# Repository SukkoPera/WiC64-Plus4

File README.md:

# WiC+4
WiC+4 is a wireless interface based on the ESP32 chip for the Commodore +4.

## Summary
This is just a customization of [the original WiC64 project](https://github.com/WiC64-Team/wic64-hardware) in order to make it work on the Commodore +4. In fact, while this computer features a User Port that looks very similar to the one you can find on the C64, the electrical connections are different and thus some modifications are required.

The board should also be usable on a C16 or C116 through [a User Port card](https://github.com/SukkoPera/16up).

Apart from the functional changes:
* I have added a jumper that selects whether the ESP should be powered by the rectified +9VAC or by the 5V rail.
* Consequently, I have added a ferrite on the 5V rail. An axial inductor should also fit, some experimentation will show what is better.
* I have switched the resistor footprints to 0805 for easier hand solderability.

The board keeps exactly the same size and major component layout, so all enclosures should still be usable.

## Usage
One of my goals was to make the modifications in a way such that **no changes would be required on the firmware side**.

Nevertheless, **this thing is completely unusable at the moment**, since no computer-side software exists.

What needs to be done is to take [this library](https://github.com/WiC64-Team/wic64-library) and adapt it so that:

* Data I/O takes place through the User Port
* The PC2 signal (ack/strobe: byte read from/written to port, rising edge) is controlled through /DTR
* The PA2 signal (Direction: HIGH = C64/+4 => ESP, LOW = ESP => C64/+4) is controlled through /RTS
* The FLAG2 signal (ack/strobe: byte read from/written to port, falling edge) can be read through /DCD.

/DTR and /RTS can be controlled through bits 0 and 3 (respectively) of $FD02 (Note that there is an inverter gate inbetween, so they are not really active-low).

/DCD can be read through bit 4 of $FD01 (again, mind the inverter gate). An interrupt can also be set up to track its changes if required.

I recommend taking a quick look at the 6551 ACIA datasheet in order to understand how to treat the other bits properly.

Another recommendation would be to make the User Port/ACIA base addresses configurable, for those who might want to use the 16UP board in External mode.

I had actually done part of the above work, only to find out that **I would then need a "launcher" program that is not open source, so I decided to stop all development**.

Please refer to [the original project](https://github.com/WiC64-Team/wic64-hardware) for all documentation, firmware, drivers, etc.

## Assembly
If you decide to use power from the 5V rail, the diode bridge and 220uF cap can be skipped.

The ESP-01 board in the top right corner is only required for debugging.

## Releases
If you want to get this board produced, you are recommended to get [the latest release](https://github.com/SukkoPera/WiC64-Plus4/releases) rather than the current git version, as the latter might be under development and is not guaranteed to be working.

Every release is accompanied by its Bill Of Materials (BOM) file and any relevant notes about it, which you are recommended to read carefully.

## License
WiC+4 is distributed under the [CC-BY 4.0 license](https://creativecommons.org/licenses/by/4.0/).

WiC+4 is provided to you ‘as is’ and without any express or implied warranties whatsoever with respect to its functionality, operability or use, including, without limitation, any implied warranties of merchantability, fitness for a particular purpose or infringement. We expressly disclaim any liability whatsoever for any direct, indirect, consequential, incidental or special damages, including, without limitation, lost revenues, lost profits, losses resulting from business interruption or loss of data, regardless of the form of action or legal theory under which the liability may be asserted, even if advised of the possibility or likelihood of such damages.

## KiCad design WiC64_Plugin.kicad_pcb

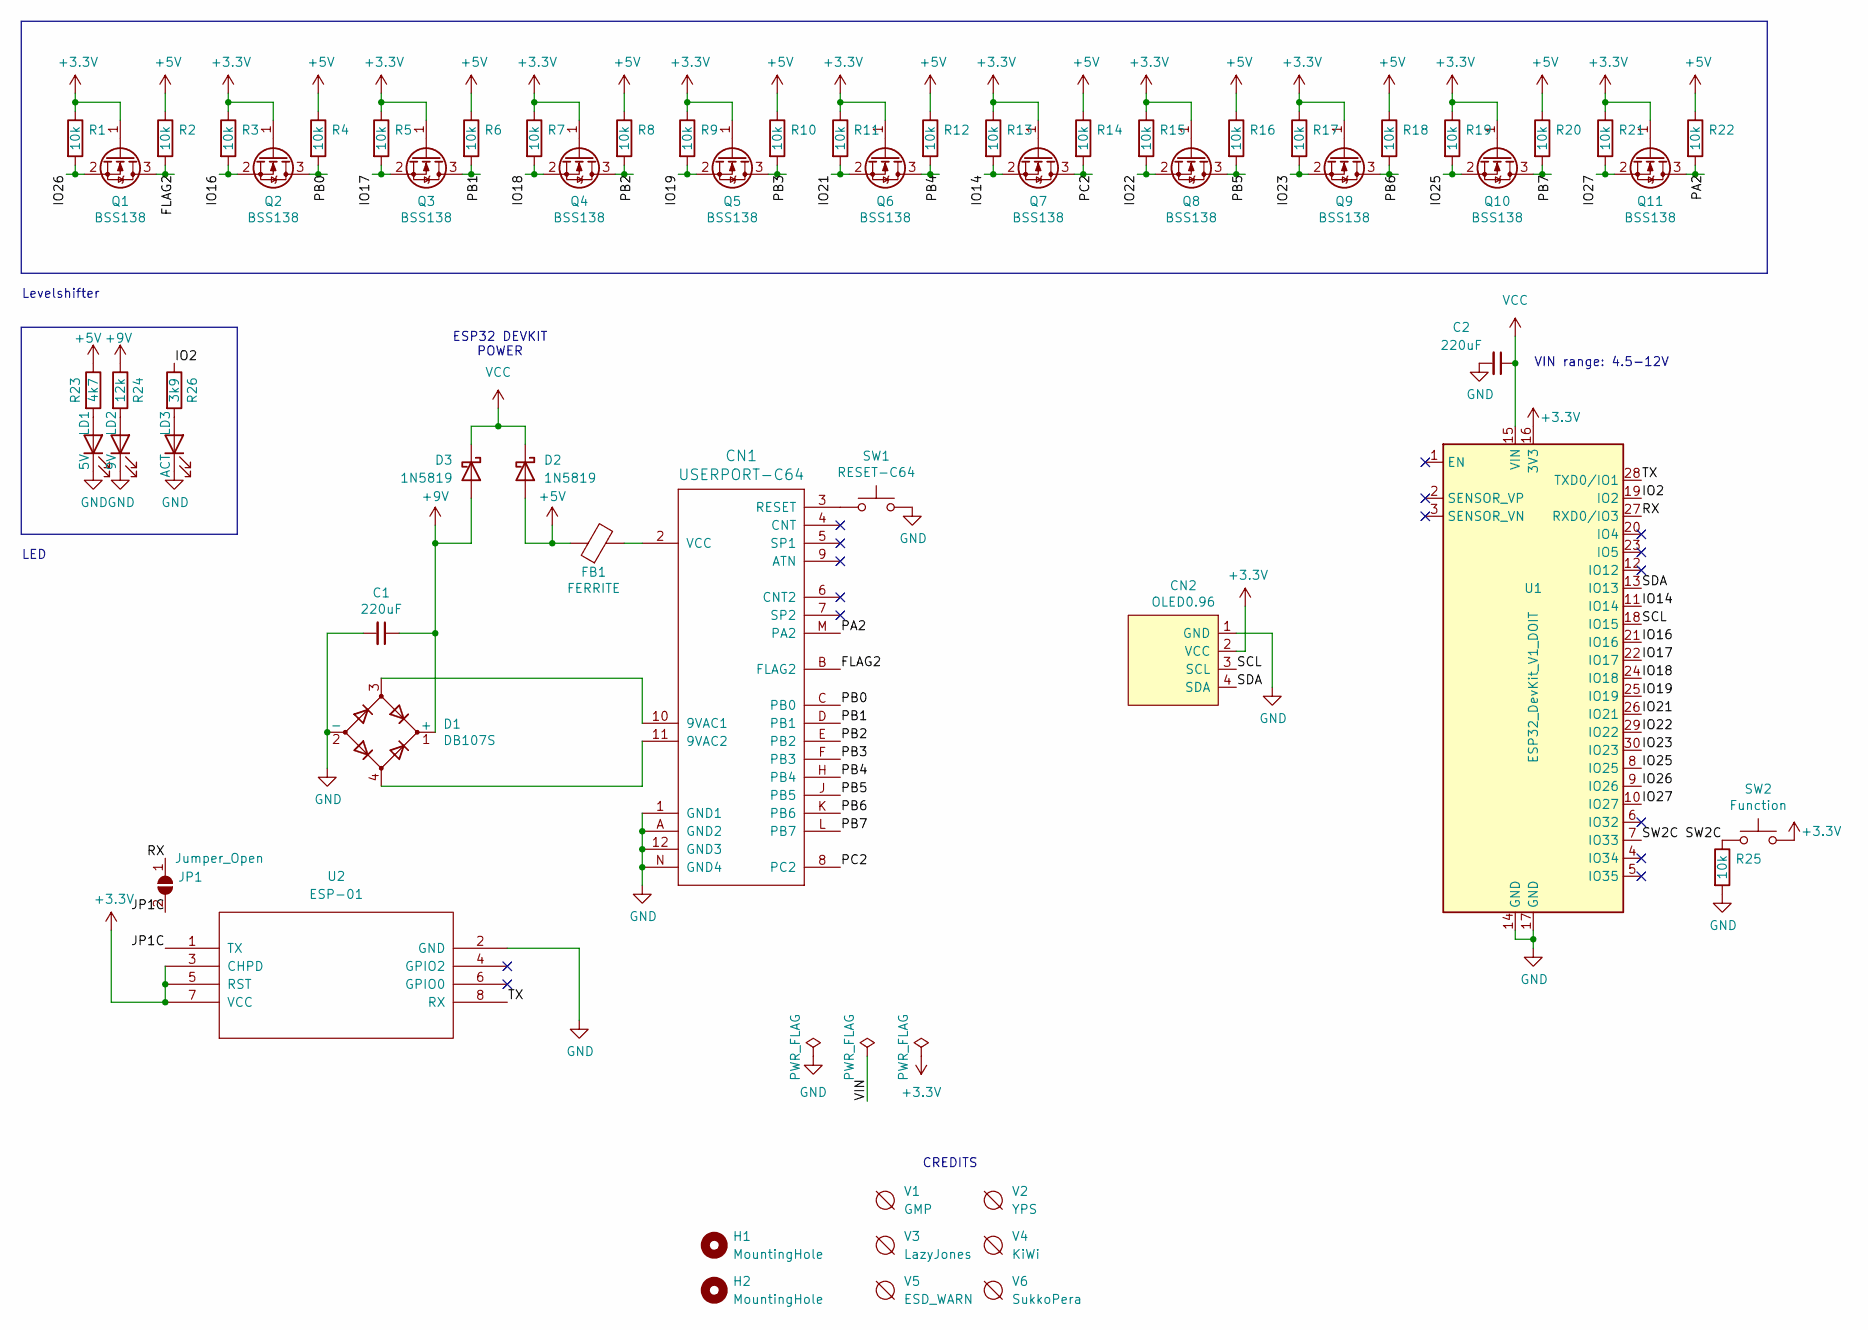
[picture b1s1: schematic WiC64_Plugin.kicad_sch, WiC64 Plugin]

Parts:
C1: 220uF; CP_6.3x11mm_horiz-R; LCSC C269997
C2: 220uF; CP_6.3x11mm_horiz-R; LCSC C106598
CN1: USERPORT-C64; UPS24CONN
CN2: OLED0.96; PinSocket_1x04_P2.54mm_Vertical
D1: DB107S; Diode_Bridge_Diotec_SO-DIL-Slim; LCSC C190797
D2, D3: 1N5819; D_SMA; LCSC C402219
FB1: FERRITE; Ferrite_D6.0mm_L10.00mm_Horizontal
H1, H2: MountingHole; MountingHole_3.2mm_M3_ISO7380
JP1: Jumper_Open; SolderJumper-2_P1.3mm_Open_RoundedPad1.0x1.5mm
LD1: 5V; LED_D3.0mm; LCSC C568936
LD2: 9V; LED_D3.0mm; LCSC C568937
LD3: ACT; LED_D3.0mm; LCSC C331056
Q1, Q2, Q3, Q4, Q5, Q6, Q7, Q8, Q9, Q10, Q11: BSS138; SOT-23; LCSC C112239
R1, R2, R3, R4, R5, R6, R7, R8, R9, R10, R11, R12, R13, R14, R15, R16, R17, R18, R19, R20, R21, R22, R25: 10k; R_0805_2012Metric_Pad1.20x1.40mm_HandSolder; LCSC C25804
R23: 4k7; R_0805_2012Metric_Pad1.20x1.40mm_HandSolder; LCSC C23162
R24: 12k; R_0805_2012Metric_Pad1.20x1.40mm_HandSolder; LCSC C22790
R26: 3k9; R_0805_2012Metric_Pad1.20x1.40mm_HandSolder; LCSC C23018
SW1: RESET-C64; SW_Tactile_SPST_Angled_PTS645Vx58-2LFS; LCSC C406160
SW2: Function; SW_Tactile_SPST_Angled_PTS645Vx58-2LFS; LCSC C406160
U1: ESP32_DevKit_V1_DOIT; esp32_devkit_v1_doit
U2: ESP-01
V1: GMP
V2: YPS; YPS2
V3: LazyJones; LazyJones2
V4: KiWi
V5: ESD_WARN; ESD-Logo_6.6x6mm_SilkScreen
V6: SukkoPera; PearLogo

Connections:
+3.3V: CN2.2 (VCC), Q1.1 (G), Q2.1 (G), Q3.1 (G), Q4.1 (G), Q5.1 (G), Q6.1 (G), Q7.1 (G), Q8.1 (G), Q9.1 (G), Q10.1 (G), Q11.1 (G), R1.1, R3.1, R5.1, R7.1, R9.1, R11.1, R13.1, R15.1, R17.1, R19.1, R21.1, SW2.2, U1.16 (3V3), U2.3 (CHPD), U2.5 (RST), U2.7 (VCC)
+5V: D2.2 (A), FB1.1, R2.1, R4.1, R6.1, R8.1, R10.1, R12.1, R14.1, R16.1, R18.1, R20.1, R22.1, R23.1
+9V: C1.1, D1.1 (+), D3.2 (A), R24.1
/FLAG2: CN1.B (FLAG2), Q1.3 (D), R2.2
/IO2: R26.1, U1.19 (IO2)
/IO14: Q7.2 (S), R13.2, U1.11 (IO14)
/IO16: Q2.2 (S), R3.2, U1.21 (IO16)
/IO17: Q3.2 (S), R5.2, U1.22 (IO17)
/IO18: Q4.2 (S), R7.2, U1.24 (IO18)
/IO19: Q5.2 (S), R9.2, U1.25 (IO19)
/IO21: Q6.2 (S), R11.2, U1.26 (IO21)
/IO22: Q8.2 (S), R15.2, U1.29 (IO22)
/IO23: Q9.2 (S), R17.2, U1.30 (IO23)
/IO25: Q10.2 (S), R19.2, U1.8 (IO25)
/IO26: Q1.2 (S), R1.2, U1.9 (IO26)
/IO27: Q11.2 (S), R21.2, U1.10 (IO27)
/JP1C: JP1.2 (B), U2.1 (TX)
/PA2: CN1.M (PA2), Q11.3 (D), R22.2
/PB0: CN1.C (PB0), Q2.3 (D), R4.2
/PB1: CN1.D (PB1), Q3.3 (D), R6.2
/PB2: CN1.E (PB2), Q4.3 (D), R8.2
/PB3: CN1.F (PB3), Q5.3 (D), R10.2
/PB4: CN1.H (PB4), Q6.3 (D), R12.2
/PB5: CN1.J (PB5), Q8.3 (D), R16.2
/PB6: CN1.K (PB6), Q9.3 (D), R18.2
/PB7: CN1.L (PB7), Q10.3 (D), R20.2
/PC2: CN1.8 (PC2), Q7.3 (D), R14.2
/RX: JP1.1 (A), U1.27 (RXD0/IO3)
/SCL: CN2.3 (SCL), U1.18 (IO15)
/SDA: CN2.4 (SDA), U1.13 (IO13)
/SW2C: R25.1, SW2.1, U1.7 (IO33)
/TX: U1.28 (TXD0/IO1), U2.8 (RX)
GND: C1.2, C2.2, CN1.1 (GND1), CN1.12 (GND3), CN1.A (GND2), CN1.N (GND4), CN2.1 (GND), D1.2 (-), LD1.1 (K), LD2.1 (K), LD3.1 (K), R25.2, SW1.2, U1.14 (GND), U1.17 (GND), U2.2 (GND)
unnamed: CN1.10 (9VAC1), D1.3
unnamed: CN1.11 (9VAC2), D1.4
unnamed: CN1.3 (RESET), SW1.1
unnamed: CN1.2 (VCC), FB1.2
unnamed: LD1.2 (A), R23.2
unnamed: LD2.2 (A), R24.2
unnamed: LD3.2 (A), R26.2
VCC: C2.1, D2.1 (K), D3.1 (K), U1.15 (VIN)

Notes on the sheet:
VIN range: 4.5-12V
CREDITS
Levelshifter
LED
ESP32 DEVKIT POWER

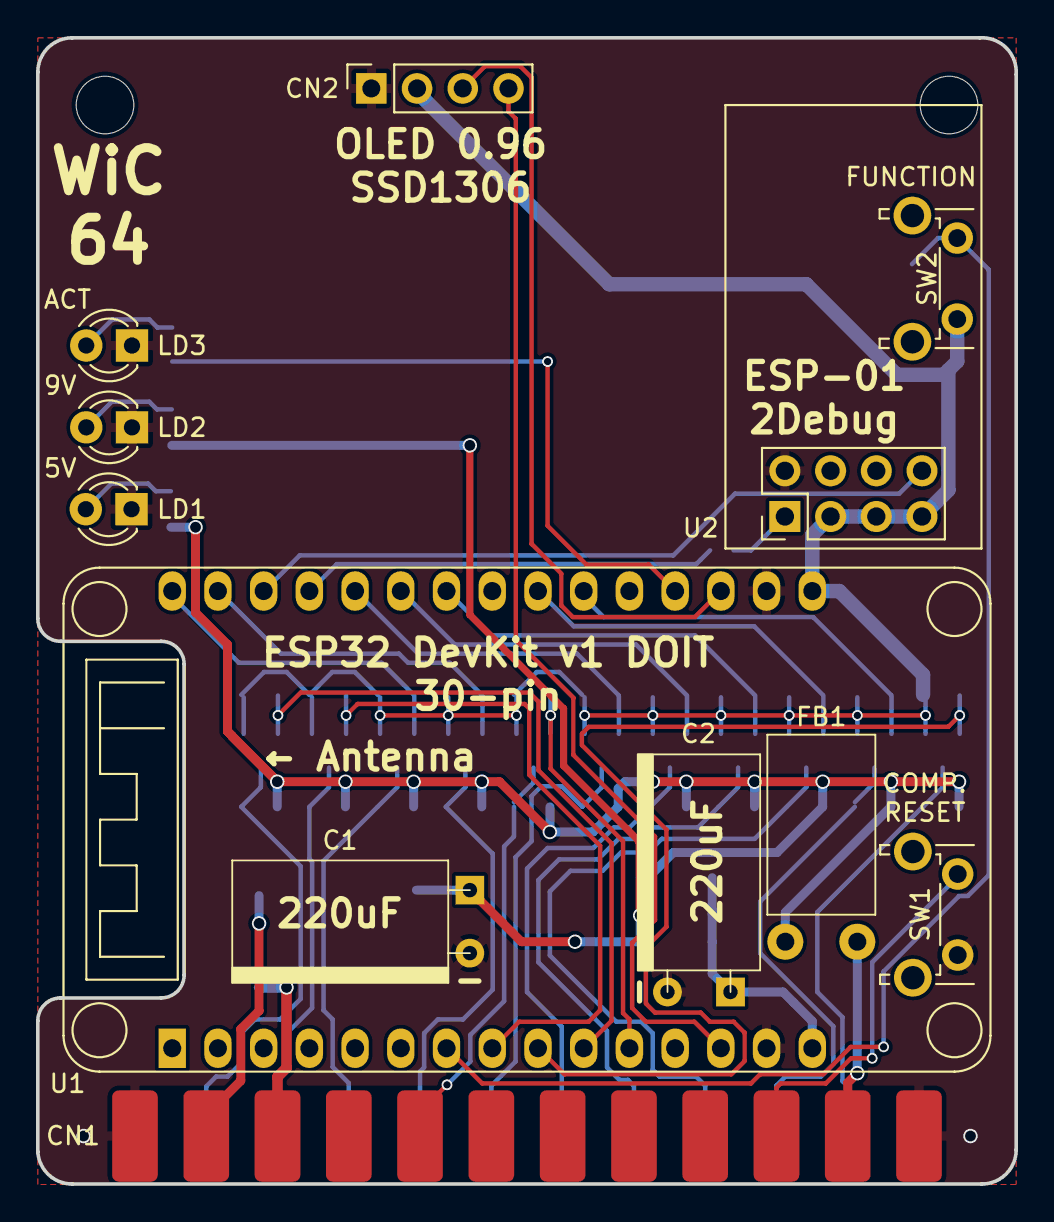
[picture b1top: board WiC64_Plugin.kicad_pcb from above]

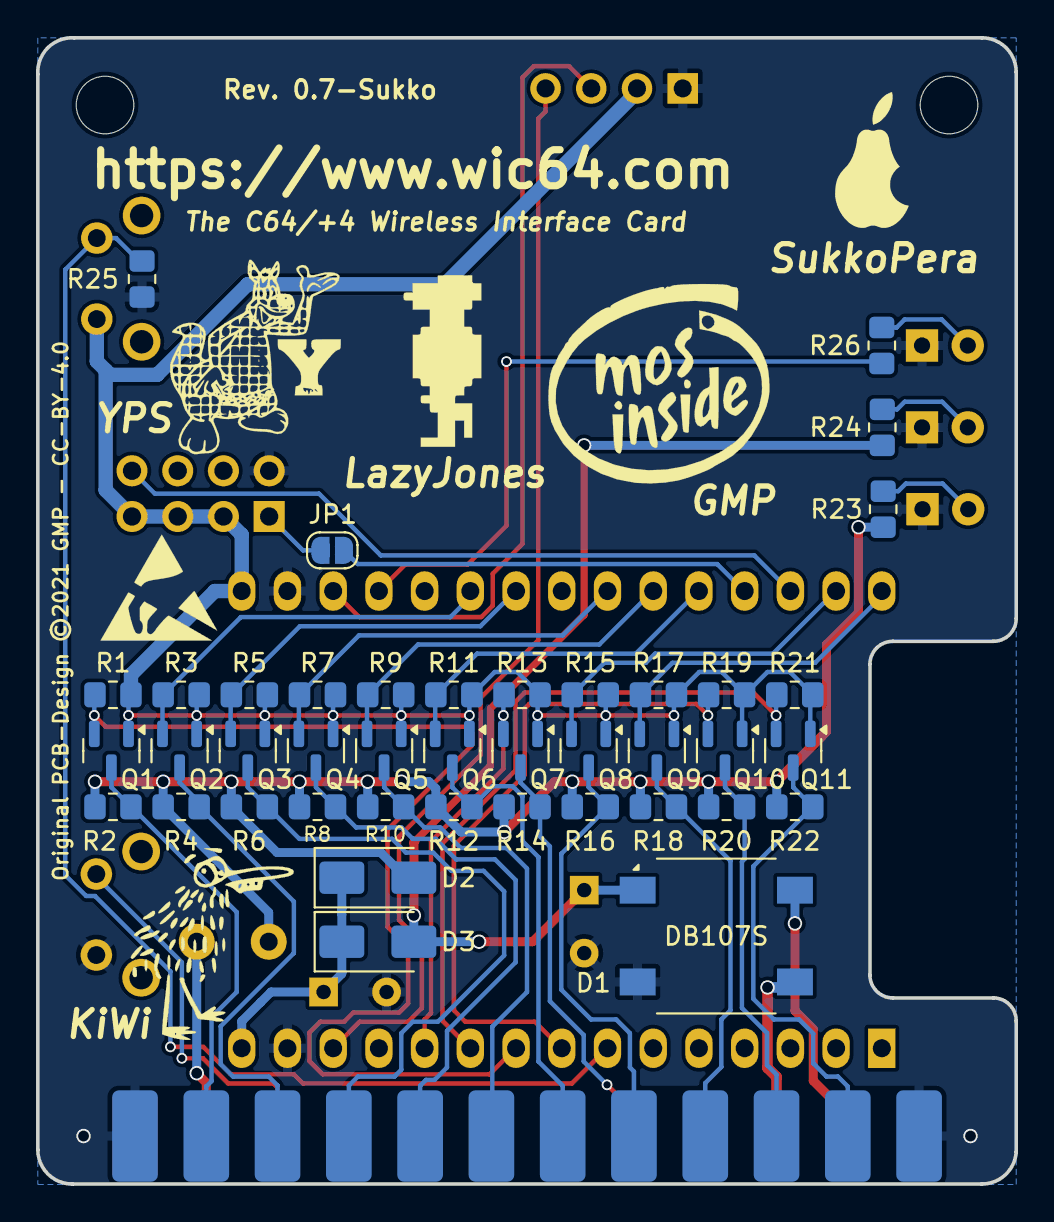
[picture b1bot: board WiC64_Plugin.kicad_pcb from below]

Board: 2 copper layers, 54.4 x 63.7 mm, 61 parts (47 on the bottom side), 41 nets.

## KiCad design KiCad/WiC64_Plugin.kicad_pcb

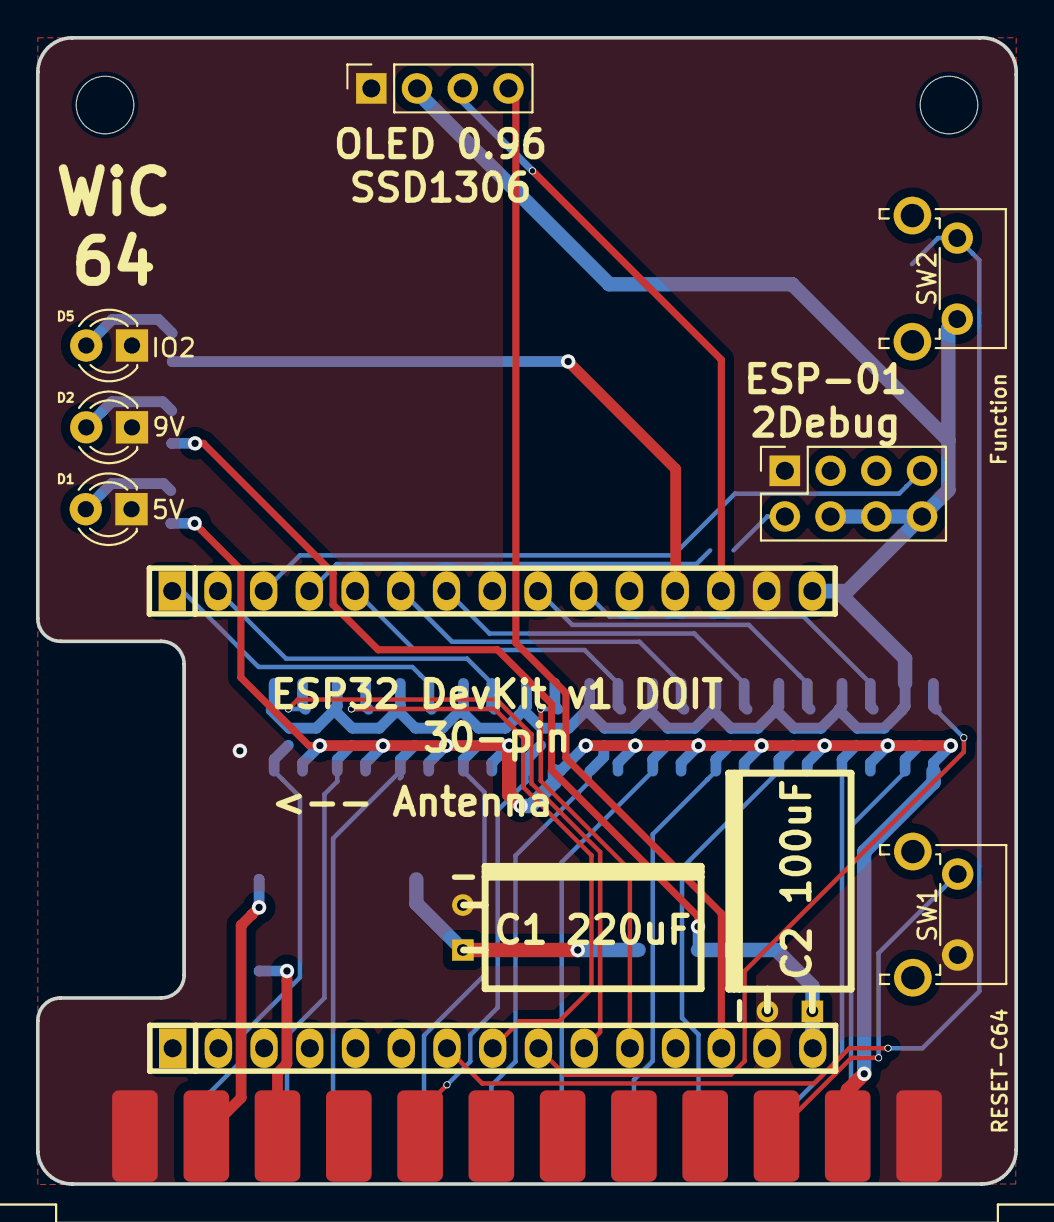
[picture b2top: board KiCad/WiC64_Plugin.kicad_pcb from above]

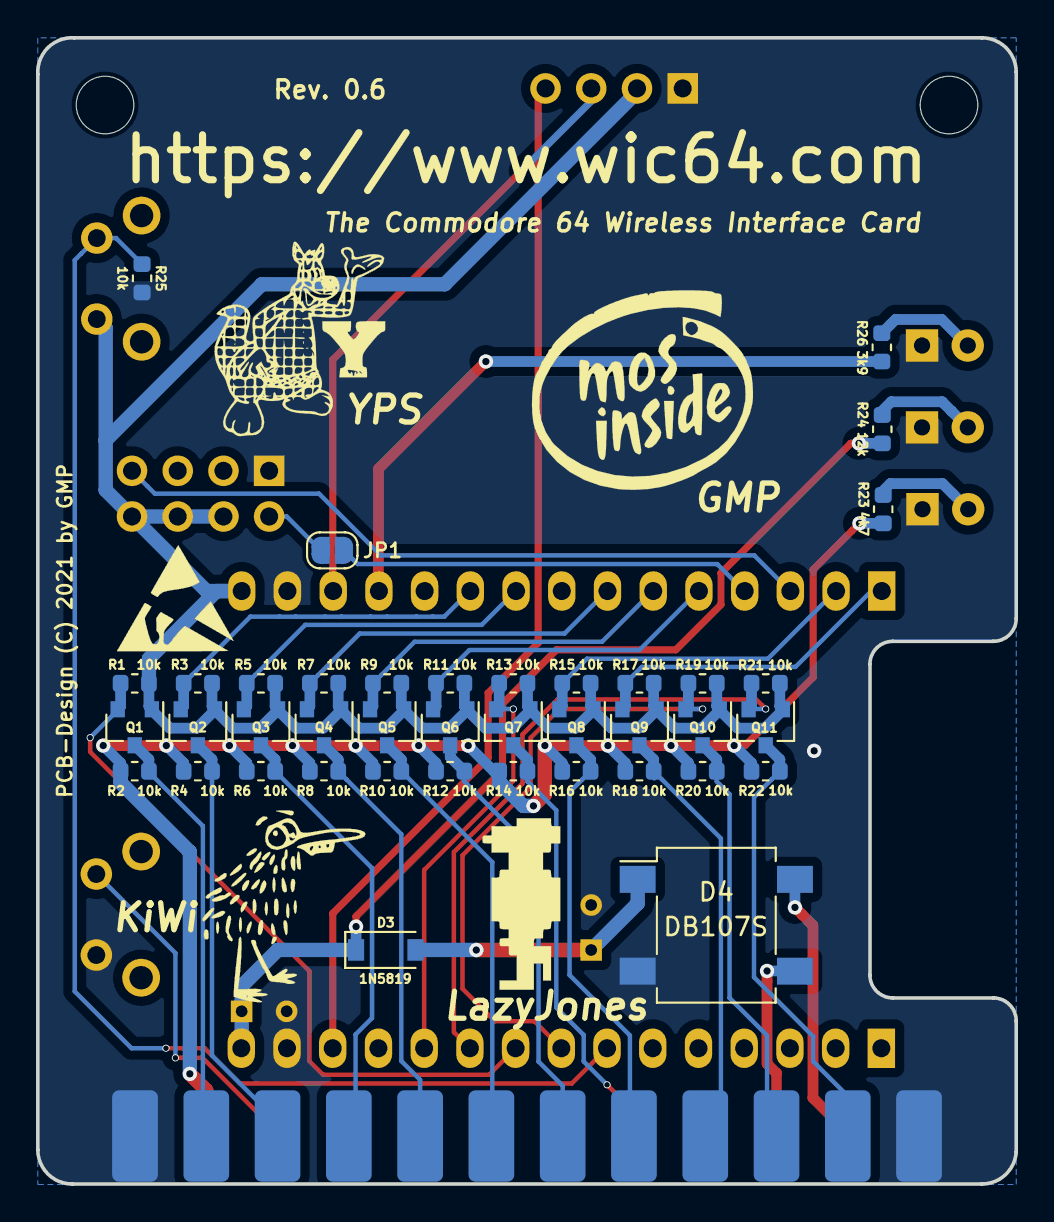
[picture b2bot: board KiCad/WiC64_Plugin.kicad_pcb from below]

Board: 2 copper layers, 54.4 x 63.7 mm, 52 parts (40 on the bottom side), 40 nets.

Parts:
C1: 220uF; CP_6.3x11mm_hor
C2: 100uF; CP_6.3x11mm_hor
CN1: USERPORT-C64; UPS24CONN
D1: 5V; LED_D3.0mm
D2: 9V; LED_D3.0mm
D3: 1N5819; D_SOD-123
D4: DB107S; Diode_Bridge_Diotec_SO-DIL-Slim
D5: IO2; LED_D3.0mm
JP1: Jumper_Open; SolderJumper-2_P1.3mm_Open_RoundedPad1.0x1.5mm
Q1, Q2, Q3, Q4, Q5, Q6, Q7, Q8, Q9, Q10, Q11: BSS138; SOT-23
R1, R2, R3, R4, R5, R6, R7, R8, R9, R10, R11, R12, R13, R14, R15, R16, R17, R18, R19, R20, R21, R22, R25: 10k; R_0603_1608Metric
R23: 4k7; R_0603_1608Metric
R24: 12k; R_0603_1608Metric
R26: 3k9; R_0603_1608Metric
SW1: RESET-C64; SW_Tactile_SPST_Angled_PTS645Vx58-2LFS
SW2: Function; SW_Tactile_SPST_Angled_PTS645Vx58-2LFS
XBrd1: Conn_01x04_Female; PinSocket_1x04_P2.54mm_Vertical
XU1-1, XU1-2: Conn_01x15_Female; pin_socket_15
XU2: HEADER_4x2; PinSocket_2x04_P2.54mm_Vertical

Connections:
+3.3V: Q1.1 (G), Q2.1 (G), Q3.1 (G), Q4.1 (G), Q5.1 (G), Q6.1 (G), Q7.1 (G), Q8.1 (G), Q9.1 (G), Q10.1 (G), Q11.1 (G), R1.1, R3.1, R5.1, R7.1, R9.1, R11.1, R13.1, R15.1, R17.1, R19.1, R21.1, SW2.2, XBrd1.2, XU1-2.15, XU2.4, XU2.6, XU2.8
+5V: CN1.2 (VCC), R2.1, R4.1, R6.1, R8.1, R10.1, R12.1, R14.1, R16.1, R18.1, R20.1, R22.1, R23.1
/FLAG2: CN1.B (FLAG2), Q1.3 (D), R2.2
/IO2: R26.1, XU1-2.12
/IO14: Q7.2 (S), R13.2, XU1-1.11
/IO16: Q2.2 (S), R3.2, XU1-2.10
/IO17: Q3.2 (S), R5.2, XU1-2.9
/IO18: Q4.2 (S), R7.2, XU1-2.7
/IO19: Q5.2 (S), R9.2, XU1-2.6
/IO21: Q6.2 (S), R11.2, XU1-2.5
/IO22: Q8.2 (S), R15.2, XU1-2.2
/IO23: Q9.2 (S), R17.2, XU1-2.1
/IO25: Q10.2 (S), R19.2, XU1-1.8
/IO26: Q1.2 (S), R1.2, XU1-1.9
/IO27: Q11.2 (S), R21.2, XU1-1.10
/JP1C: JP1.2 (B), XU2.2
/PA2: CN1.M (PA2), Q11.3 (D), R22.2
/PB0: CN1.C (PB0), Q2.3 (D), R4.2
/PB1: CN1.D (PB1), Q3.3 (D), R6.2
/PB2: CN1.E (PB2), Q4.3 (D), R8.2
/PB3: CN1.F (PB3), Q5.3 (D), R10.2
/PB4: CN1.H (PB4), Q6.3 (D), R12.2
/PB5: CN1.J (PB5), Q8.3 (D), R16.2
/PB6: CN1.K (PB6), Q9.3 (D), R18.2
/PB7: CN1.L (PB7), Q10.3 (D), R20.2
/PC2: CN1.8 (PC2), Q7.3 (D), R14.2
/RX: JP1.1 (A), XU1-2.4
/SCL: XBrd1.3, XU1-2.13
/SDA: XBrd1.4, XU1-1.13
/SW2C: R25.1, SW2.1, XU1-1.7
/TX: XU1-2.3, XU2.7
/VIN: C2.1, D3.1 (K), R24.1, XU1-1.15
GND: C1.2, C2.2, CN1.1 (GND1), CN1.12 (GND3), CN1.A (GND2), CN1.N (GND4), D1.1 (K), D2.1 (K), D4.2 (-), D5.1 (K), R25.2, SW1.2, XBrd1.1, XU1-1.14, XU1-2.14, XU2.1
unnamed: CN1.10 (9VAC1), D4.3
unnamed: CN1.11 (9VAC2), D4.4
unnamed: CN1.3 (RESET), SW1.1
unnamed: D1.2 (A), R23.2
unnamed: D2.2 (A), R24.2
unnamed: C1.1, D3.2 (A), D4.1 (+)
unnamed: D5.2 (A), R26.2

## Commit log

2024-05-24 Fix board outline (and port to KiCad 8)
2024-05-24 Find/Reconstruct missing libs/footprints and fix most DRC problems PCB is mostly untouched so far, focus was just on "completing" the released source files
2024-05-25 Add .gitignore
2024-05-25 Move all files to root directory
2024-05-25 Make all resistors 0805
2024-05-25 Add 3D models
2024-05-26 Remove redundant symbols
2024-05-26 Allow powering ESP32 from 5V
2024-05-26 Update gerber path
2024-05-26 Move all footprints to single library
2024-05-28 Initial +4 version
2024-06-02 Complete changes for +4 version
2024-06-07 Add renders
2024-06-14 Final touches for C64 version
2024-06-14 Move SCL/SDA tracks around
2024-06-23 Latch FLAG2
2024-06-23 Final touches for V1FF
2024-09-09 Add Schmitt trigger to clean TX signal
2025-01-21 Various refinements for V1FFF
2025-01-21 Final-final-final touches
2025-11-24 Add diode so that power source is selected automatically
2025-11-24 Add Pear logo + Connect 9V power led to actual 9V

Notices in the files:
KiCad/WiC64_Plugin.kicad_pcb:
(C) 2021 by GMP
PCB-Design (C) 2021 by GMP
WiC64_Plugin.kicad_pcb:
Original PCB-Design ©2021 GMP - CC-BY-4.0
